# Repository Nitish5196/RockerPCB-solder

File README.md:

# RocketPCB-solder
A rocket shaped PCB which vibrates and lights up (flashing to imitate a lauching rocket) when the button is pressed , it can be used as a cool looking keychain<br>
BOM(Bill Of Materials):<ul>
<li>Battery Holders x2</li>
<li>555 timer x1</li>
<li>Transistors x8</li>
<li>Resistors x10</li>
<li>photoresistor x 1</li>
<li> potentiometer x1</li>
<li>LED x6</li>
<li>push button x1</li>
<li>motor x1</li>
<li>Capacitor x2</li>
</ul><br>
<B>Screenshots</B><br>

<br>
<b>Slack Username:</b><u>Nitish Kumar</u> <br>
display name:<u>Mr_KN5196</u>
<b>slack  id:</b>U0BQHGZ64CA

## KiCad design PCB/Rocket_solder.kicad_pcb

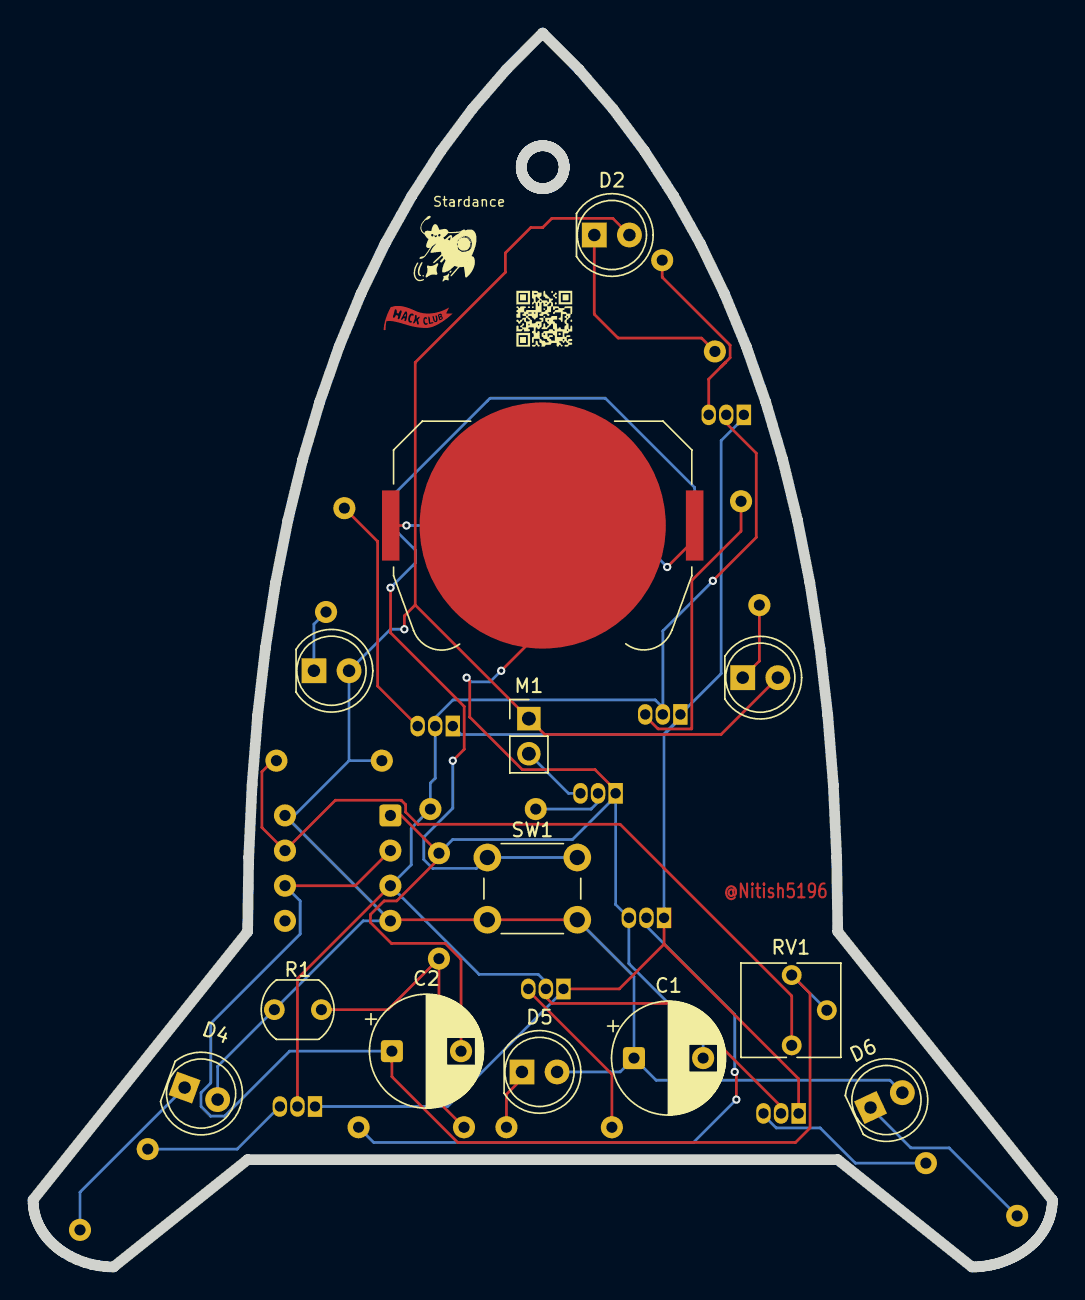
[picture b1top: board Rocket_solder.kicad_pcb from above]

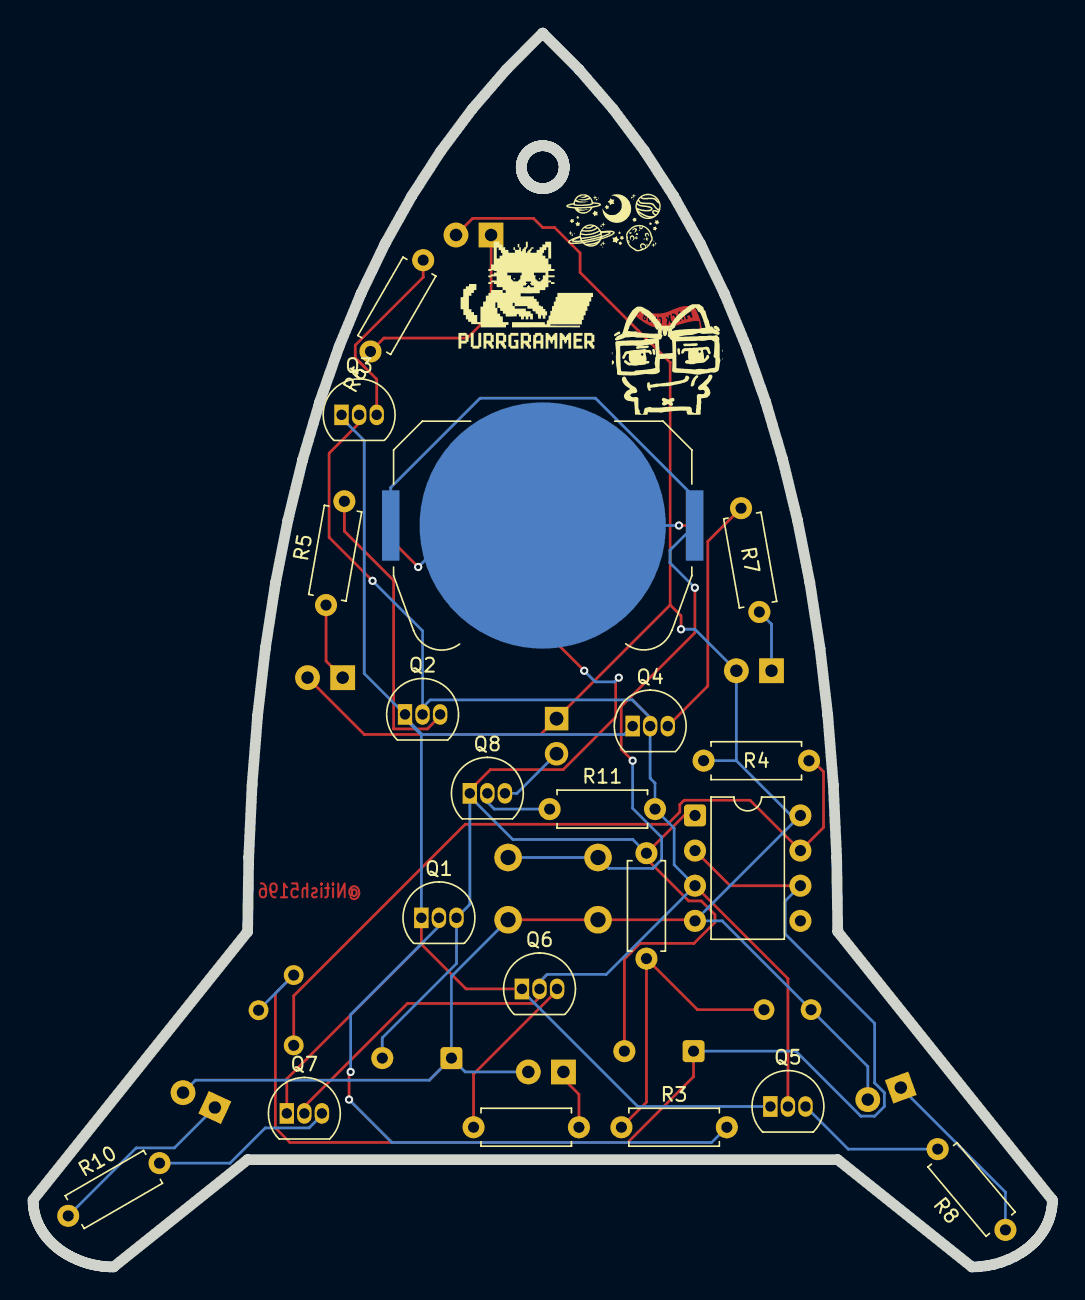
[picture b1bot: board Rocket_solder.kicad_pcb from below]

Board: 2 copper layers, 73.7 x 89.2 mm, 33 parts (20 on the bottom side), 24 nets.

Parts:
BT1, BT2: Battery_Cell; BatteryHolder_Keystone_3034_1x20mm
C1: C_Polarized; CP_Radial_D8.0mm_P5.00mm
C2: 10uF; CP_Radial_D8.0mm_P5.00mm
D1, D3, D4, D5, D6: LED; LED_D5.0mm
D2: POWER; LED_D5.0mm
M1: Motor_DC; PinHeader_1x02_P2.54mm_Vertical
Q1, Q2, Q3, Q4, Q5, Q6, Q7, Q8: 2N3904; TO-92_Inline
R1: 47k; R_LDR_5.1x4.3mm_P3.4mm_Vertical
R2, R3, R4, R11: 4.7k; R_Axial_DIN0207_L6.3mm_D2.5mm_P7.62mm_Horizontal
R5, R6, R7, R8, R9, R10: 220; R_Axial_DIN0207_L6.3mm_D2.5mm_P7.62mm_Horizontal
RV1: 100k; Potentiometer_Vishay_T73YP_Vertical
SW1: SW_Push; SW_PUSH_6mm
U1: LM555xN; DIP-8_W7.62mm

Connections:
+6V: C1.1, D1.2 (A), D2.2 (A), D3.2 (A), D4.2 (A), D5.2 (A), D6.2 (A), M1.1 (+), R1.1, R4.1, SW1.2, U1.4 (~RST), U1.8 (VCC)
/CLK_OUT: Q2.2 (B), Q3.2 (B), Q4.2 (B), Q5.2 (B), Q6.2 (B), Q7.2 (B), R11.2, U1.3 (OUT)
/LIGHT_ENABLE: Q1.1 (C), Q2.1 (E), Q3.1 (E), Q4.1 (E), Q5.1 (E), Q6.1 (E), Q7.1 (E)
GND: BT1.2 (-), C1.2, C2.2, Q1.3 (E), Q8.1 (E), R2.2, U1.1 (GND)
unnamed: BT1.1 (+), BT2.2 (-)
unnamed: BT2.1 (+), SW1.1
unnamed: D1.1 (K), R5.1
unnamed: D2.1 (K), R6.1
unnamed: D3.1 (K), R7.1
unnamed: D4.1 (K), R8.1
unnamed: D5.1 (K), R9.1
unnamed: D6.1 (K), R10.1
unnamed: M1.2 (-), Q8.3 (C)
unnamed: Q1.2 (B), R3.2
unnamed: Q2.3 (C), R5.2
unnamed: Q3.3 (C), R6.2
unnamed: Q4.3 (C), R7.2
unnamed: Q5.3 (C), R8.2
unnamed: Q6.3 (C), R9.2
unnamed: Q7.3 (C), R10.2
unnamed: Q8.2 (B), R11.1
unnamed: R1.2, R2.1, R3.1
unnamed: R4.2, RV1.1, U1.7 (DISCH)
unnamed: C2.1, RV1.2, RV1.3, U1.2 (TRIG), U1.6 (THRES)
